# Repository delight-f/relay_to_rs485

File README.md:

# Relay to RS485

Mirror relay states over an RS-485 bus using the Modbus protocol.

## Overview

An ESP32-S2 reads up to five zero-voltage relay contacts and mirrors their
state onto an RS-485 bus as Modbus coils, so an external master can switch
the corresponding output relays. Developed for amateur radio: retrofitting
an existing proprietary system to allow coil switching — moving antenna
directors or changing bands. Designed to work with commonly available
RS-485 relay boards (AliExpress, eBay, etc.).

The repository contains both the firmware and the KiCad PCB design.

## Repository layout

```
.
├── relay_to_rs485/          # Arduino sketch (firmware)
│   ├── relay_to_rs485.ino   # entry point, setup()/loop()
│   └── debounce.h           # host-testable input debouncer
├── test/
│   └── test_debounce.cpp    # host unit tests for the debouncer
├── Hardware/
│   └── relay_to_rs485/      # KiCad 7 project + gerbers (REV_B)
├── Makefile                 # build/test entry point (arduino-cli)
├── sketch.yaml              # arduino-cli sketch configuration
└── .github/workflows/ci.yml # host tests + firmware build
```

## Hardware

The PCB has eight input pins hardwired; the current firmware uses five,
leaving room for future relay expansion. It was designed around an 8-relay
board.

- KiCad project: [`Hardware/relay_to_rs485/`](Hardware/relay_to_rs485/)
- Manufacturing files (REV_B gerbers):
  [`Hardware/relay_to_rs485/gerbers/`](Hardware/relay_to_rs485/gerbers/)

## Firmware

- Board: LOLIN S2 Mini (ESP32-S2)
- Framework: Arduino, built with [arduino-cli](https://arduino.github.io/arduino-cli/)
- Modbus: [ModbusMaster](https://github.com/4-20ma/ModbusMaster) 2.0.1
- Input filtering: ESP32 hardware glitch filter + software debounce
  (`debounce.h`, host-testable)

### Prerequisites

- [arduino-cli](https://arduino.github.io/arduino-cli/latest/installation/) ≥ 1.0
- ESP32 core and ModbusMaster library:

```bash
arduino-cli config add board_manager.additional_urls \
  https://espressif.github.io/arduino-esp32/package_esp32_index.json
arduino-cli core update-index
arduino-cli core install esp32:esp32
arduino-cli lib install ModbusMaster@2.0.1
```

### Build and flash

```bash
git clone git@github.com:delight-f/relay_to_rs485.git
cd relay_to_rs485
make            # build firmware
make upload     # build and flash over USB
```

Or without make:

```bash
arduino-cli compile --fqbn esp32:esp32:lolin_s2_mini relay_to_rs485
arduino-cli compile --fqbn esp32:esp32:lolin_s2_mini relay_to_rs485 --upload
```

### Test

The debounce logic is pure C++ and unit-tested on the host — no Arduino
required:

```bash
make test
```

### Configuration

Pin assignments, Modbus slave ID, and channel count are named `constexpr`
constants at the top of `relay_to_rs485/relay_to_rs485.ino`. Adjust these
to match your wiring before flashing.

| Constant | Default | Meaning |
| --- | --- | --- |
| `kModbusSlaveId` | `255` | Modbus slave ID |
| `kModbusBaud` | `9600` | RS-485 baud rate (8E1) |
| `kModbusRxPin` / `kModbusTxPin` | `31` / `35` | RS-485 UART pins |
| `kNumChannels` | `5` | Number of input/coil pairs |
| `kInputPins` | `15, 17, 18, 19, 20` | Input pins (active-low, pull-up) |
| `kCoilAddresses` | `0x0000…0x0004` | Modbus coil addresses |
| `kPollIntervalMs` | `50` | Loop poll interval |
| `kDebounceMs` | `30` | Software debounce window |
| `kMaxWriteRetries` | `3` | Modbus write retry count |

Inputs are active-low: pull-up means HIGH = relay not active (`false`),
LOW = relay active (`true`).

## Versioning

This project uses [SemVer](https://semver.org/).

## Contributing

Issues and pull requests are welcome. Please open an issue to discuss
significant changes before submitting a PR.

## License

Creative Commons Attribution-ShareAlike 4.0 International License.
See [LICENSE](./LICENSE) for details.

## Acknowledgments

- [ModbusMaster](https://github.com/4-20ma/ModbusMaster) library
- [arduino-cli](https://arduino.github.io/arduino-cli/) toolchain

## Authors

- **de_light** — initial work

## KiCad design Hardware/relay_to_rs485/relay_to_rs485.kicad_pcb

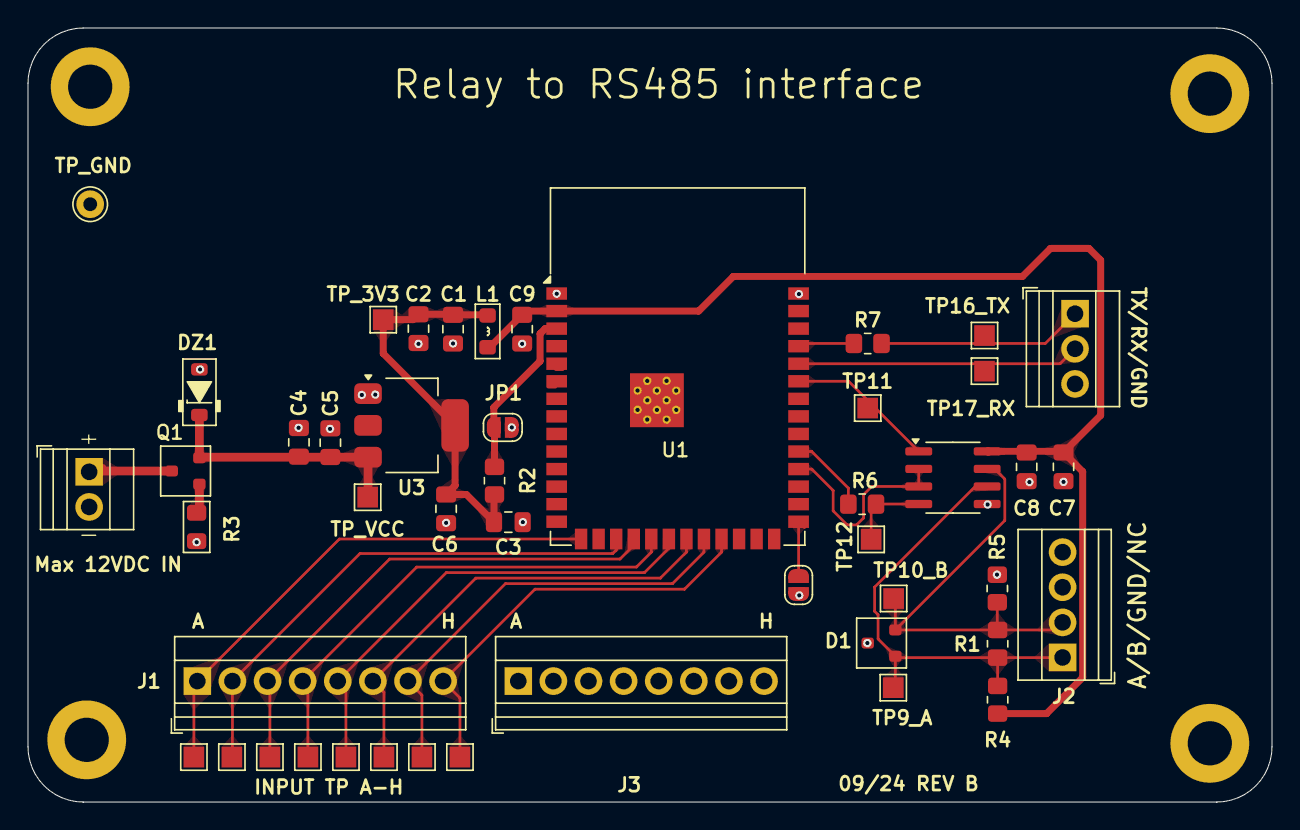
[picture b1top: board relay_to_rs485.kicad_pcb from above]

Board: 2 copper layers, 90.0 x 56.0 mm, 47 parts (0 on the bottom side), 24 nets.

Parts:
C1, C3, C5, C8, C9: 0.1uF; C_0805_2012Metric_Pad1.18x1.45mm_HandSolder
C2, C4, C7: 1uF; C_0805_2012Metric_Pad1.18x1.45mm_HandSolder
C6: 22uF; C_0805_2012Metric_Pad1.18x1.45mm_HandSolder
D1: SM712 TVS; SOT-23
DZ1: 7.5 or 8.2; D_SOD-123_Zener
J1: Relay Inputs A to E connected; TerminalBlock_Xinya_XY308-2.54-8P_1x08_P2.54mm_Horizontal
J2: RS485 Output Screw Terminal; TerminalBlock_Xinya_XY308-2.54-4P_1x04_P2.54mm_Horizontal
J3: Screw_Terminal_InputGrounds; TerminalBlock_Xinya_XY308-2.54-8P_1x08_P2.54mm_Horizontal
J4: Max 12VDC IN; TerminalBlock_Xinya_XY308-2.54-2P_1x02_P2.54mm_Horizontal
J5: UART OUT; TerminalBlock_Xinya_XY308-2.54-3P_1x03_P2.54mm_Horizontal
JP1: EN_RST; SolderJumper-2_P1.3mm_Open_RoundedPad1.0x1.5mm
JP2: PROG; SolderJumper-2_P1.3mm_Open_RoundedPad1.0x1.5mm
L1: 2.2nH; L_0805_2012Metric_Pad1.05x1.20mm_HandSolder
Q1: IRLML6401; SOT-23
R1: 100R; R_0805_2012Metric_Pad1.20x1.40mm_HandSolder
R2: 4.7k; R_0805_2012Metric_Pad1.20x1.40mm_HandSolder
R3: 100R; R_0805_2012Metric_Pad1.15x1.40mm_HandSolder
R4, R5: 330R; R_0805_2012Metric_Pad1.20x1.40mm_HandSolder
R6, R7: 470R; R_0805_2012Metric_Pad1.20x1.40mm_HandSolder
TP1_A1, TP2_B1, TP3_C1, TP4_D1, TP5_E1, TP6_F1, TP7_G1, TP9_A, TP10_B, TP11, TP12, TP13_3V3, TP15_VCC1, TP16_TX, TP17_RX: TestPoint_Pad_1.5x1.5mm
TP8_H1: TestPoint_Probe; TestPoint_Pad_1.5x1.5mm
TP14_GND1: Pin_D1.0mm_L10.0mm
U1: ESP32-S3-WROOM-1
U2: MAX485E; SOIC-8_3.9x4.9mm_P1.27mm
U3: SMX1117MP-3.3; SOT-223-3_TabPin2

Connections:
+3V3: C1.1, C2.1, C3.1, C6.1, C7.1, C8.1, C9.1, L1.1, L1.2, R2.1, R4.1, TP13_3V3.1, U1.2 (3V3), U2.8 (VCC), U3.2 (VO)
/A+: D1.1 (A1), J2.1, R1.1, R4.2, TP9_A.1, U2.6 (A)
/B-: D1.2 (A2), J2.2, R1.2, R5.1, TP10_B.1, U2.7 (B)
/InputA: J1.1, TP1_A1.1, U1.15 (IO3)
/InputB: J1.2, TP2_B1.1, U1.17 (IO9)
/InputC: J1.3, TP3_C1.1, U1.18 (IO10)
/InputD: J1.4, TP4_D1.1, U1.19 (IO11)
/InputE: J1.5, TP5_E1.1, U1.20 (IO12)
/InputF: J1.6, TP6_F1.1, U1.21 (IO13)
/InputG: J1.7, TP7_G1.1, U1.22 (IO14)
/InputH: J1.8, TP8_H1.1, U1.23 (IO21)
/RX: J5.2, TP17_RX.1, U1.36 (RXD0)
/TX: J5.1, R7.1, TP16_TX.1
GND: C1.2, C2.2, C3.2, C4.2, C5.2, C6.2, C7.2, C8.2, C9.2, D1.3 (Com), DZ1.2 (A), J2.3, J3.1, J3.2, J3.3, J3.4, J3.5, J3.6, J3.7, J3.8, J4.2, J5.3, JP1.2 (B), JP2.2 (B), R3.2, R5.2, TP14_GND1.1, U1.1 (GND), U1.40 (GND), U1.41 (GND), U2.5 (GND), U3.1 (GND)
unnamed: JP1.1 (A), R2.2, U1.3 (EN)
unnamed: JP2.1 (A), U1.27 (IO0)
unnamed: J4.1, Q1.3 (D)
unnamed: Q1.1 (G), R3.1
unnamed: U1.30 (IO37), U2.2 (~RE), U2.3 (DE)
unnamed: R6.2, U1.31 (IO38)
unnamed: TP11.1, U1.35 (IO42), U2.1 (RO)
unnamed: R7.2, U1.37 (TXD0)
unnamed: R6.1, TP12.1, U2.4 (DI)
VCC: C4.1, C5.1, DZ1.1 (K), Q1.2 (S), TP15_VCC1.1, U3.3 (VI)

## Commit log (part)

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2024-08-28 Initial creation
    Initial creation of Git
2024-08-28 Update main.cpp
    Updated some code, not sure if it will work.
2024-09-03 Initial upload
    Initial upload - preproduction draft of REV A
2024-09-03 Minor rotation of J2 labelling on schematic
2024-09-06 various edits
2024-09-06 More edits
    Change of library...
2024-09-06 update mb.task() routine
2024-09-06 board updates
2024-09-08 Change to ModBusMaster Library
    Reduction in delay time from 2000ms to 300ms
2024-09-08 General formatting, Whitesmiths style
2024-09-08 remove gpio.h
    Unnecessary library
2024-09-08 Changed decoupling resistor values from 100uF to 1uF
    Too high capacitance
    Also changed silkscreen for R1 to make clear terminating resistor
2024-09-08 Update README.md
    Update title
2024-09-08 Rename License.MD to LICENSE.MD
2024-09-09 Change of DC polarity marking on PCB
2024-09-09 Change ModBus terminology
2024-09-09 Revert "Change ModBus terminology"
    This reverts commit 4fc38e3de870ae543c7cbb347975141097b8e9a8.
2024-09-10 Revision B of Board (2.0.0)
    Add:
    1. LC filter on 3.3V input
    2. Change trace widths to 20mil for 3.3V and 25mil for VCC as per Espressif documentation
    3. Add-in 470R UART Tx resistors to suppress 80MHz harmonics
    4. Rerouting of components around MAX3485 chip
    5. Change value of R2 EN pullup resistor to 4.7k
2024-09-10 Minor change
2024-09-10 Forgot TP_GND
2024-09-10 Fiddling around with TP_GND position
2024-09-19 v2.0.1
    Board layout improvements
2024-09-19 Corrected reverse D-S pins for IRLM6401 Q1
2024-09-19 More reworking of board
    Addition of ZD1, MOSFET RP protection diode, reconfig of JP1 etc
2024-09-20 More changes
2024-09-20 Moved writing mark to back silkscreen
2024-09-27 Pin changes for ESP32-S3-WROOM board
    Changes from LOLIN S2 Mini prototyping board pins to ESP-S3-WROOM in preparation for production
    Note only pins first five pins are connected, others are left for redundancy.

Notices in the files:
README.md:
License: CC BY-SA 4.0
